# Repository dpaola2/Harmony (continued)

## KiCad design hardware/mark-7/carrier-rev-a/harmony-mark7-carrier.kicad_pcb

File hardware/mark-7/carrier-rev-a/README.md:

# Mark-7 removable Feather carrier, revision A

The first carrier design is ready for an unpowered fit review. It replaces the Feather's loose jumper connections with sockets and labeled solder pads. Dave adopted this direction on October 11, 2026. Build Mark-7 portable Bluetooth player (HARMONY-19) tracks physical acceptance.

The existing Feather, faceplate components, firmware, battery connector, and ANO cable remain in use. The carrier is a passive two-layer PCB, nominally 53.5 × 28.3 × 1.6 mm. The PCBWay Gerber package is prepared for quotation. Physical fit remains pending; no fabrication has been released. See [submission details](pcbway/README.md).

## What connects where

The Feather plugs into two female socket strips. Ten wires run between the carrier and the display/SD board. Those wires require soldering at their endpoints. The carrier removes the need to solder onto the Feather's male pins.

The ANO STEMMA QT cable connects directly to the Feather. The battery connects directly to its JST socket. P11 and R1 reserve optional ANO interrupt wiring. Leave both unused for the current cable-only sleep behavior.

| Pad | Display label / function | Feather connection |
| --- | --- | --- |
| P1 | VIN | 3V3, JP1 pin 15 |
| P2 | GND | GND, JP1 pin 13 |
| P3 | TFT CS | GPIO26, JP1 pin 12 |
| P4 | SD CS | GPIO25, JP1 pin 11 |
| P5 | LITE | GPIO4, JP1 pin 7 |
| P6 | MISO | GPIO21, JP1 pin 4 |
| P7 | MOSI | GPIO27, JP3 pin 6 |
| P8 | DC | GPIO33, JP3 pin 7 |
| P9 | RST | GPIO32, JP3 pin 9 |
| P10 | SCK | GPIO14, JP3 pin 10 |
| P11 | Optional ANO INT | GPIO34, JP1 pin 10 |

Display VIN receives Feather 3V3. The display's separate 3Vo pin stays disconnected. Display reset does not connect to Feather RESET. Firmware uses GPIO14 and GPIO27 for clock and MOSI, rather than the Feather's default SPI pins.

R1 accepts an optional 10k axial resistor between 3V3 and ANO INT. Installing it does not enable interrupt wake in firmware. The optional wake setting and physical INT lead are separate requirements.

## Mechanical changes

The modeled assembly retains the accepted 64 × 105 × 34 mm body. A revised rear tray lowers the carrier supports and raises the USB opening by 6.45 mm. The existing printed rear tray cannot directly accept this stack.

Four M2 × 6 mm self-tapping screws secure the carrier. Each screw uses a 2 mm printed spacer under its head. Nominal thread engagement is 2.4 mm. The Feather stays removable and is held by the socket contacts; retention still needs physical testing.

The selected sockets are Samtec SSW-116-01-G-S and SSW-112-01-G-S. Their body height is 8.51 mm. The model assumes a 2.54 mm plastic body on the existing male headers. These are specific socket dimensions, not a promise that any female header will fit.

Socket tails leave only 0.66 mm nominal clearance above the tray floor before solder fillets. Check actual solder height before final assembly. Wire bends, QT/JST plugs, and removal access also need a physical check.

The carrier has a cutout beneath the vendor antenna rectangle. It does not provide a full RF clearance zone. Closed-case Bluetooth range remains unqualified.

## Print and test the small fit kit first

Open [mark7-carrier-fit-kit.3mf](print/mark7-carrier-fit-kit.3mf) as geometry in the slicer. It contains eight separate objects on a 118.5 × 50.41 mm area. The file is unsliced and contains no printer settings. Use the established PLA profile; consider a brim for the narrow socket stand-ins.

| Part | Quantity | Purpose |
| --- | --- | --- |
| Mount test base | 1 | Tests the four short supports and screw engagement |
| Carrier dummy | 1 | Matches the PCB outline, thickness, and holes |
| Long socket stand-in | 1 | Represents the 16-position socket, 8.51 mm high |
| Short socket stand-in | 1 | Represents the 12-position socket, 8.51 mm high |
| Screw spacer | 4 | Adds 2 mm under each M2 × 6 screw head |

1. Use the spare Feather first. Disconnect USB and the battery.
2. Place the carrier dummy over the four supports on the test base.
3. Put one printed spacer under each M2 × 6 screw head.
4. Start all four screws, then tighten gently. Stop if a support splits or the screw bottoms out.
5. Place the long socket stand-in over the 16-hole row and the short one over the 12-hole row.
6. Align the Feather's headers with the stand-ins. Its USB socket faces the short, unnotched end of the carrier.
7. Lower the Feather gently. Do not force pins through undersized printed holes.
8. Check that the existing black header bodies rest on the socket stand-ins without bending the Feather.
9. Check that the carrier stays flat and the screws hold without protruding through the base.
10. Report any rocking, pin mismatch, blocked USB access, or interference with the screw heads.

The printed stand-ins have clearance holes, not electrical contacts. They test spacing and stack height only. Real sockets require 3.68–6.35 mm pin insertion; confirm exposed pin length before purchase. The printed test cannot qualify contact force or electrical reliability.

After this test, review the revised rear tray with the actual cable routing. Keep the working faceplate wiring intact until the physical fit is accepted. Ten suitable insulated wires will still be needed; wire stock has not been confirmed.

## Evidence and limits

- KiCad 8.0.9: zero ERC violations, zero DRC violations, and zero unconnected nets.
- Independent check: all 28 socket positions match the vendor header layout.
- Independent check: all connected PCB pads match the exported schematic netlist.
- Independent check: eight display/SD GPIO routes match the current firmware.
- Mechanical checks: 168 modeled comparisons report no collisions above the configured tolerance.
- Print checks: eight watertight single-body objects, no overlap, and a successful 3MF round trip.

These checks do not prove solderability, signal integrity, power margin, RF range, or physical fit. Socket bodies and plugs use nominal envelopes. The previously reported cracked faceplate support is not qualified by this work.

## Files and rebuilding

- `harmony-mark7-carrier.kicad_pro`, `.kicad_sch`, `.kicad_pcb`: editable KiCad project.
- `Harmony.pretty`, `Harmony.kicad_sym`: local component libraries.
- `review/schematic.pdf`: readable electrical drawing.
- `mechanical/assembly.step`: assembly model; `mechanical/tray.stl` is a candidate rear revision.
- `bom.csv`, `connections.json`: parts and pin assignments.
- `verification.json`, `mechanical/validation.json`, `print/validation.json`: check results.

Run `rebuild.sh` from this directory to rebuild the electrical files and fit kit. It uses the repository's KiCad 8.0.9 runtime and `uv`. Mechanical generation can take several minutes. Preview PNGs use the optional rendering commands in that script.

## Sources and cross-references

- [Adafruit Feather ESP32 V2 source CAD](https://github.com/adafruit/Adafruit-ESP32-Feather-V2-PCB), retained under `hardware/mark-6/carrier-rev-a/reference/`.
- [Feather pinouts](https://learn.adafruit.com/adafruit-esp32-feather-v2/pinouts).
- [Display pinouts](https://learn.adafruit.com/2-0-inch-320-x-240-color-ips-tft-display/pinouts).
- [Samtec SSW drawing](https://suddendocs.samtec.com/catalog_english/ssw_th.pdf): socket dimensions and insertion limits. Stock and pricing are not verified.
- [Mark-7 scope](../../../docs/mark-7-portable-scope.md).
- [Power and sleep](../../../docs/mark-7-power-and-sleep.md).
- [Previous rear design](../../../enclosure/mark-7/rear-review-c/README.md).

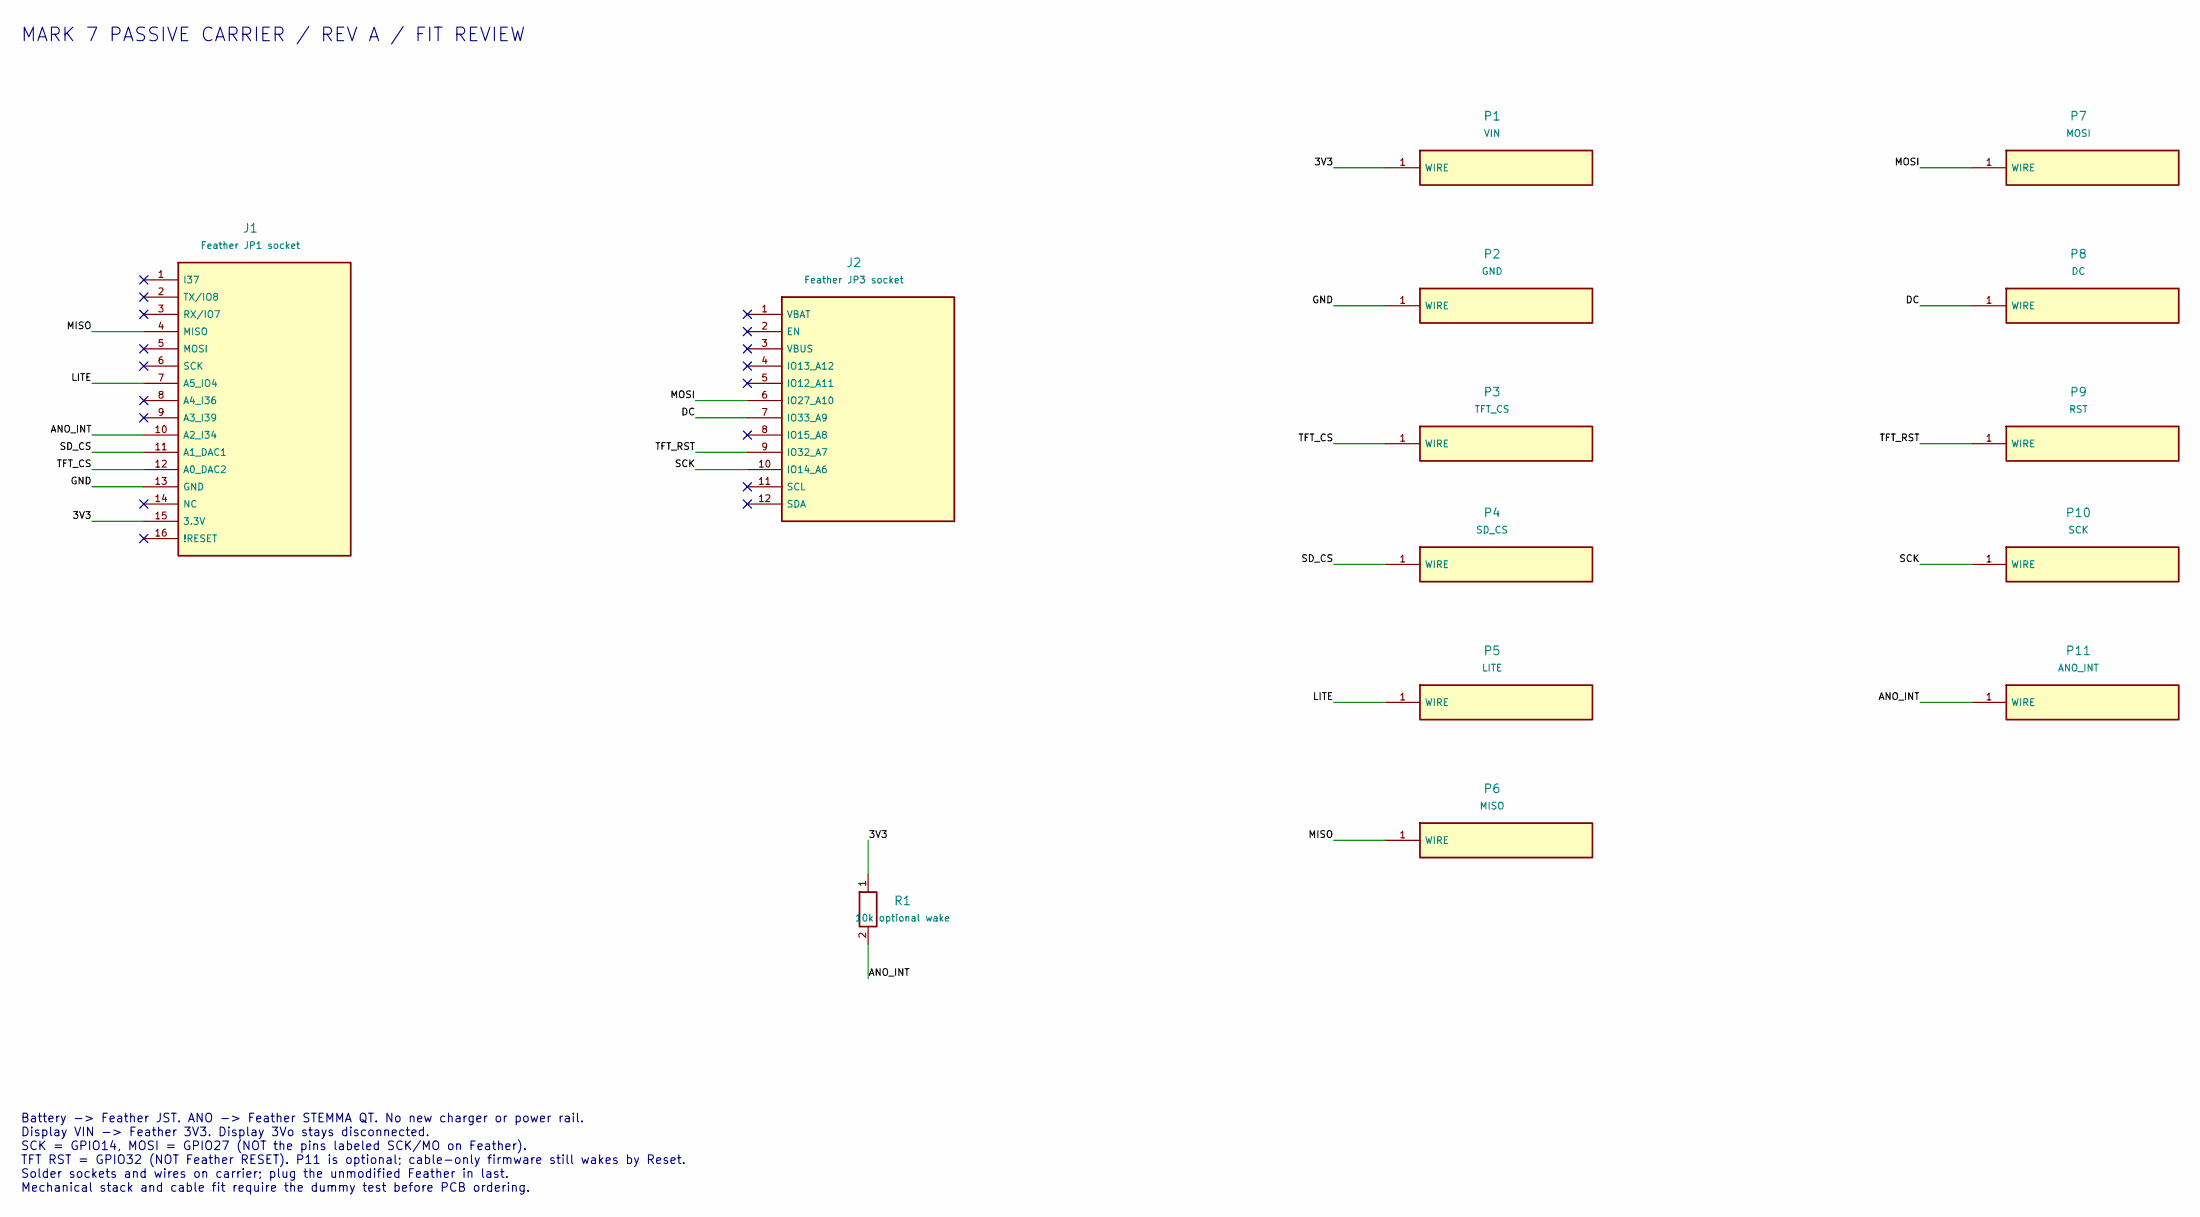
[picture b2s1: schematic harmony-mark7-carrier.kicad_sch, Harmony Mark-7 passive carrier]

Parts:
J1: Feather JP1 socket; Feather_JP1; MPN SSW-116-01-G-S
J2: Feather JP3 socket; Feather_JP3; MPN SSW-112-01-G-S
P1: VIN; WirePad
P2: GND; WirePad
P3: TFT_CS; WirePad
P4: SD_CS; WirePad
P5: LITE; WirePad
P6: MISO; WirePad
P7: MOSI; WirePad
P8: DC; WirePad
P9: RST; WirePad
P10: SCK; WirePad
P11: ANO_INT; WirePad
R1: 10k optional wake; R_Axial_P7.62

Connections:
3V3: J1.15 (3.3V), P1.1, R1.1
ANO_INT: J1.10 (A2_I34), P11.1, R1.2
DC: J2.7 (IO33_A9), P8.1
GND: J1.13 (GND), P2.1
LITE: J1.7 (A5_IO4), P5.1
MISO: J1.4 (MISO), P6.1
MOSI: J2.6 (IO27_A10), P7.1
SCK: J2.10 (IO14_A6), P10.1
SD_CS: J1.11 (A1_DAC1), P4.1
TFT_CS: J1.12 (A0_DAC2), P3.1
TFT_RST: J2.9 (IO32_A7), P9.1

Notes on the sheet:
MARK 7 PASSIVE CARRIER / REV A / FIT REVIEW
Battery -> Feather JST. ANO -> Feather STEMMA QT. No new charger or power rail. Display VIN -> Feather 3V3. Display 3Vo stays disconnected. SCK = GPIO14, MOSI = GPIO27 (NOT the pins labeled SCK/MO on Feather). TFT RST = GPIO32 (NOT Feather RESET). P11 is optional; cable-only firmware still wakes by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

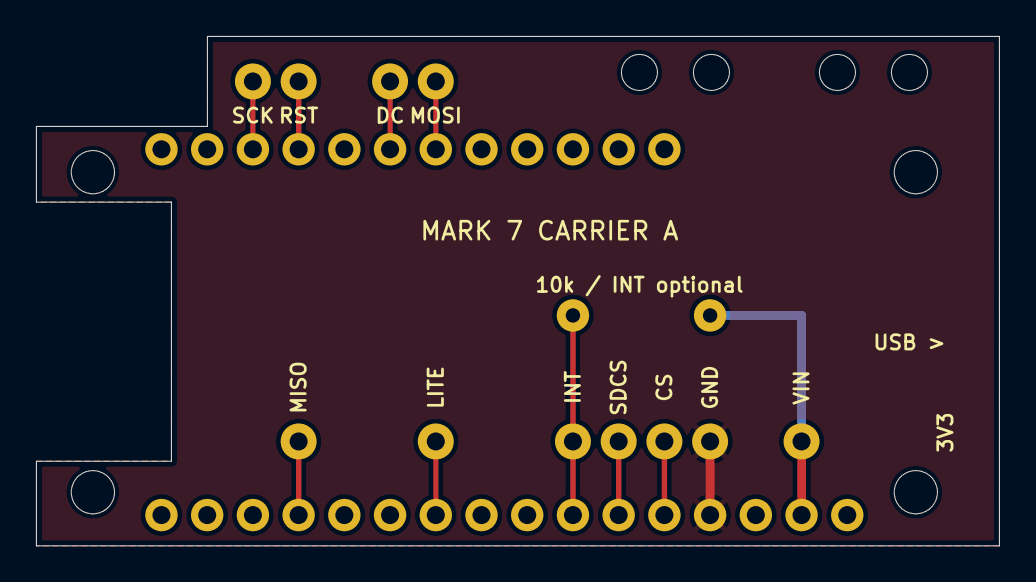
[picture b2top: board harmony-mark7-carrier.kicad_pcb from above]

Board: 2 copper layers, 53.5 x 28.3 mm, 22 parts (0 on the bottom side), 11 nets.

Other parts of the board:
H1, H2, H3, H4: M2 mount; Mount
S1, S2, S3, S4: Cable tie; Tie

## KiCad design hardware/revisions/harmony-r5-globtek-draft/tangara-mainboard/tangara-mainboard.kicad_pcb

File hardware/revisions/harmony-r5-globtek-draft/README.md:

# Harmony R5 GlobTek draft

U10 changed to MCP73871-1CCI/ML in schematic and PCB MPN property. Routed geometry and connectivity unchanged from R4. Local integration draft; not submitted or released. Temperature-sensor qualification remains open. See ../../procurement/globtek-integration/README.md.

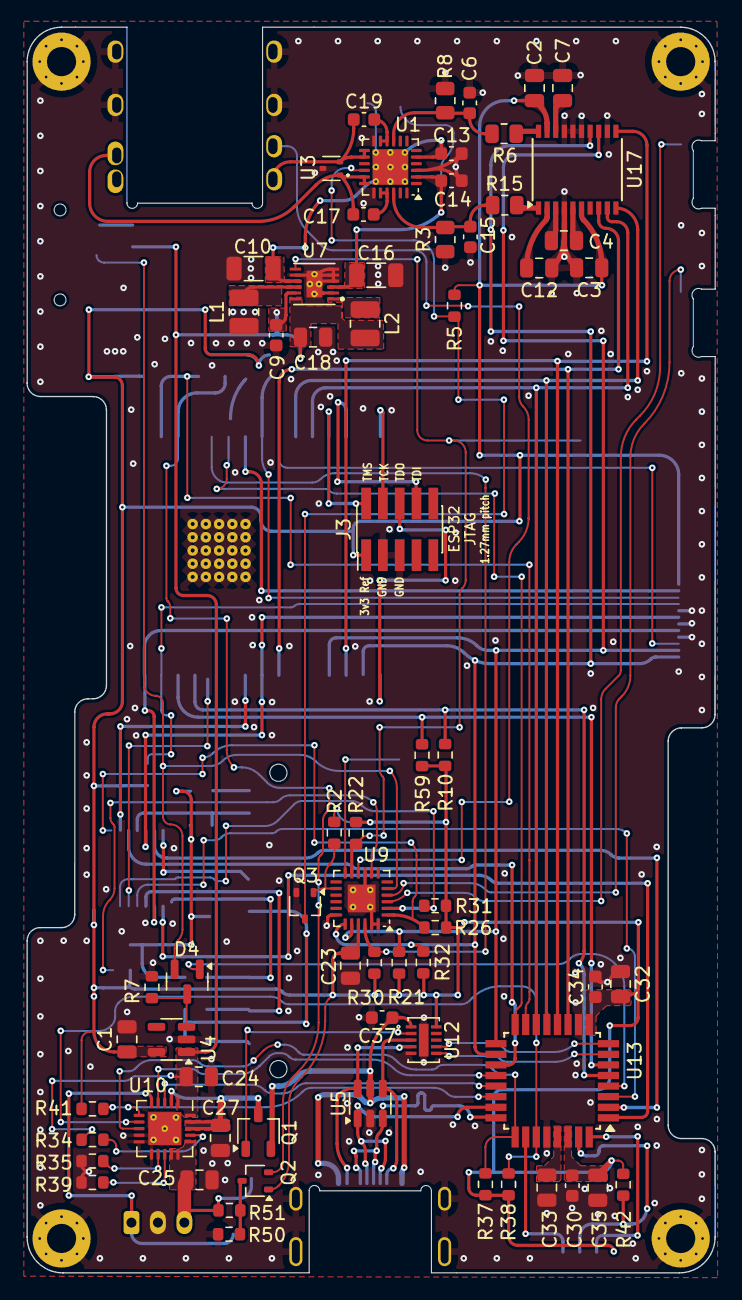
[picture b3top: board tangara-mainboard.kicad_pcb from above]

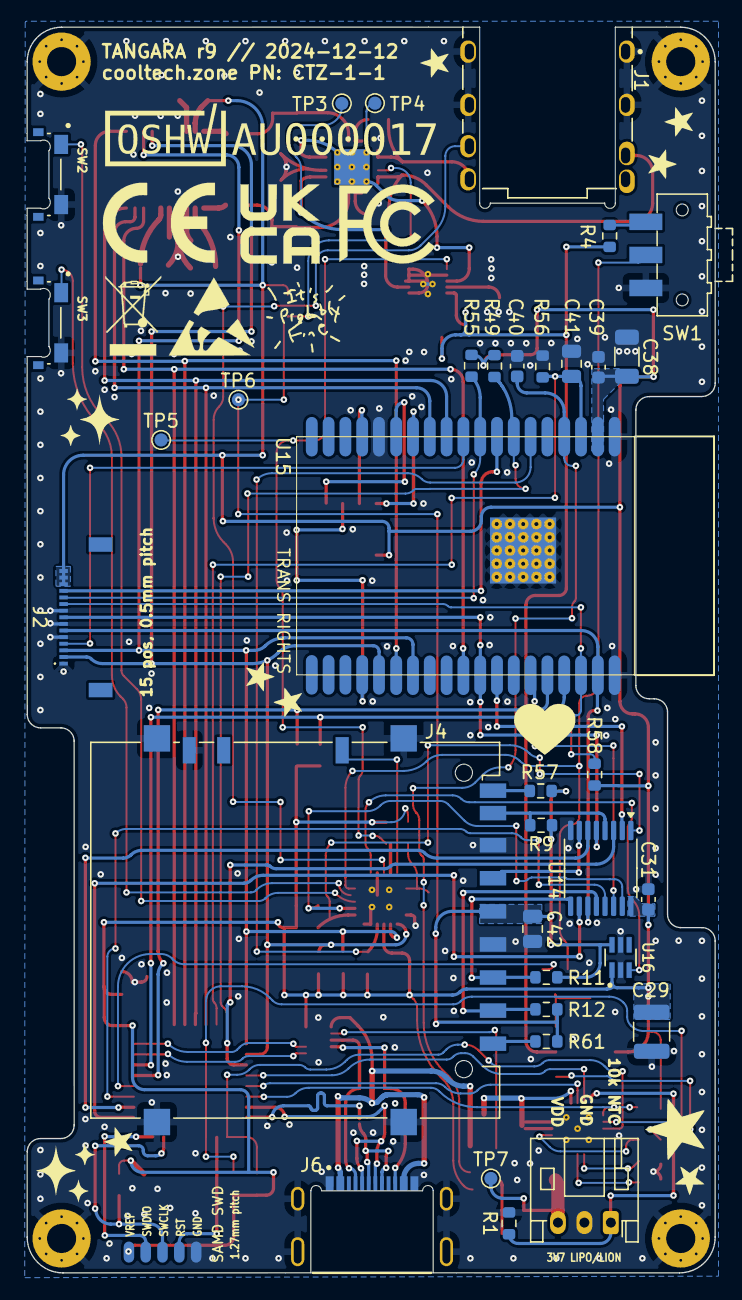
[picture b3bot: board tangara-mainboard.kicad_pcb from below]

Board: 4 copper layers, 52.0 x 94.2 mm, 106 parts (35 on the bottom side), 92 nets.

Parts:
C1, C2, C3, C7, C18, C24, C25, C27, C32, C35, C42: 10μF; C_0805_2012Metric
C4, C12, C23, C33, C41: 1μF; C_0805_2012Metric
C6, C15: 2700pF; C_0603_1608Metric
C9, C13, C14, C30, C31, C34, C37, C39, C40: 0.1μF; C_0603_1608Metric
C10, C16, C38: 22μF; C_1206_3216Metric
C17, C19: 100pF; C_0603_1608Metric
C29: 100uF; C_1210_3225Metric
D4: BAT54C; SOT-23
H1, H2, H3, H4: MountingHole; MountingHole_2.2mm_M2_Pad_Via2
J1: SJ-3506-SMT; CUI_SJ-3506-SMT
J2: FP Connector; G-Switch GT-F0509SR15-15SMT01
J3: JTAG; PinHeader_2x05_P1.27mm_Vertical_SMD
J4: SD_Card; SD_Hirose_DM1AA_SF_PEJ82
J5: SWD; SAMDSWD
J6: USB; GCT_USB4510-03-1-A_REVA
J7: Battery; JST_PH_S3B-PH-K_1x03_P2.00mm_Horizontal
L1, L2: 4.7μH; L_1008_2520Metric
Q1: PMV48XPA2R; TSOT-23
Q2, Q3: PJC138K; SOT-323_SC-70
R1, R2, R4, R5, R9, R10, R11, R12, R21, R22, R26, R30, R31, R32, R34, R35, R37, R38, R41, R49, R55, R57, R58, R59, R61: 10kΩ; R_0603_1608Metric
R3, R8: 2.2kΩ; R_0805_2012Metric
R6, R15: 560Ω; R_0805_2012Metric
R7, R50, R51, R56: 1MΩ; R_0603_1608Metric
R39, R42: 1kΩ; R_0603_1608Metric
SW1: SW_SPDT; SW_SPDT_CK-JS102011SAQN
SW2, SW3: SW_Push; SW_EVQ-P4HB3B
TP3: +5V; TestPoint_Pad_D1.0mm
TP4: -5V; TestPoint_Pad_D1.0mm
TP5: AMP_EN; TestPoint_Pad_D1.0mm
TP6: AMP_MUTE; TestPoint_Pad_D1.0mm
TP7: BAT; TestPoint_Pad_D1.0mm
U1: INA1620; QFN-24-1EP_4x4mm_P0.5mm_EP2.7x2.7mm_ThermalVias
U3: D5V0L2B3T-7; SOT-523
U4: TLV75533PDBV; SOT-23-5
U5: PE1605C4A6; SOT-23-6
U7: TPS65133; SON40P300X300X80-13N
U9: PCA8575; HVQFN-24-1EP_4x4mm_P0.5mm_EP2.1x2.1mm
U10: MCP73871; QFN-20-1EP_4x4mm_P0.5mm_EP2.5x2.5mm_ThermalVias2
U12: BD91N01NUX; BD91N01NUX-E2
U13: ATSAMD21E18A-AF; TQFP-32_7x7mm_P0.8mm
U14: 74CBTLV3257; TSSOP-16_4.4x5mm_P0.65mm
U15: ESP32-WROVER-E; ESP32-WROVER
U16: TPS22948; SOT65P210X110-6N
U17: WM8523; SSOP-20_4.4x6.5mm_P0.65mm

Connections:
3.5mm_DETECT: J1.4, U9.10 (IO1_0)
+3V3: C1.1, C2.2, C3.1, C23.1, C29.1, C30.1, C31.1, C32.2, C34.1, C35.2, C38.1, C39.1, J2.13, J2.14, J2.15, J3.1 (vRef), J5.1, Q2.1 (G), R2.2, R5.1, R10.1, R21.1, R22.2, R26.1, R30.1, R31.1, R32.1, R37.1, R38.1, R41.1, R42.1, R49.1, R55.1, R58.1, R59.1, U4.5 (OUT), U9.21 (VDD), U12.10 (VDD_IO), U13.9 (VDDANA), U13.30 (VDDIN), U14.16 (VCC), U15.2 (VDD), U16.1 (IN), U17.6 (LINEVDD), U17.19 (AVDD)
+5VA: C14.1, C16.1, TP3.1, U1.2 (V+), U7.3 (VPOS)
-5VA: C10.2, C13.1, TP4.1, U1.5 (V-), U1.25 (EP), U7.9 (VNEG)
/ESP_EN: C41.1, R56.2, U13.15 (PA14), U15.3 (EN)
/JTAG.TCK: J3.4 (TCK), U15.16 (JTAG.TCK)
/JTAG.TDI: J3.8 (TDI), U15.14 (JTAG.TDI)
/JTAG.TDO: J3.6 (TDO), U15.23 (JTAG.TDO)
/JTAG.TMS: J3.2 (TMS), U15.13 (JTAG.TMS)
/Power/NTC: J7.1, R1.1, U10.5 (THERM)
/Power/VBUS_SWITCHED: C27.1, Q1.3 (D), U10.2 (VPCC), U10.18 (IN), U10.19 (IN)
/SWD.RESET: J5.4, U13.26 (~RESET)
/SWD.SWCLK: J5.3, R42.2, U13.31 (SWCLK)
/SWD.SWDIO: J5.2, U13.32 (SWDIO)
/UART.ESP.RX: R10.2, U13.5 (PA04(SERCOM0.0)), U15.34 (UART.RX)
/UART.ESP.TX: R59.2, U13.6 (PA05(SERCOM0.1)), U15.35 (UART.TX)
/~SAMD_INT: R49.2, U13.16 (PA15), U15.7 (I35)
AMP_EN: R22.1, TP5.1, U7.7 (EN), U9.11 (IO1_1)
AMP_MUTE: Q3.3 (D), R5.2, TP6.1, U1.16 (EN)
BAT_LEVEL: C40.2, Q2.2 (S), U15.4 (ADC1_CH0/NOINT)
CHG_PROG: U10.4 (PROG2), U13.20 (PA19)
CHG_SEL: U10.3 (SEL), U13.21 (PA22)
CHG_STAT1: R37.2, U10.8 (STAT1/~LBO), U13.25 (PA27)
CHG_STAT2: R38.2, U10.7 (STAT2), U13.27 (PA28)
DAC.BCK: U13.13 (PA10(I2S/SCK)), U15.11 (I2S.BCK), U17.10 (BCLK)
DAC.DATA: U13.11 (PA08(I2S/SD)), U15.29 (I2S.DOUT), U17.8 (DACDAT)
DAC.LRCK: U13.14 (PA11(IS2/FS)), U15.12 (I2S.LRCK), U17.9 (LRCLK)
DAC.MCK: U13.12 (PA09(I2S/MCK)), U15.25 (BOOT/I2S.SCK), U17.11 (MCLK)
DISPLAY_DR: J2.11, R55.2, U15.9 (IO33)
DISPLAY_LED_EN: J2.12, U15.8 (IO32)
ESP_SPI.DISPLAY_CS: J2.10, R58.2, U15.36 (SPI.CS1)
ESP_SPI.PICO: J2.6, U14.11, U15.37 (SPI.PICO)
ESP_SPI.POCI: U14.2, U15.31 (SPI.POCI)
ESP_SPI.SCLK: J2.8, U14.5, U15.30 (SPI.CLK)
ESP_SPI.SD_CS: U14.14, U15.33 (SPI.CS0)
GND: C1.2, C2.1, C3.2, C6.1, C7.2, C9.2, C10.1, C12.1, C13.2, C14.2, C15.1, C16.2, C18.2, C23.2, C24.2, C25.2, C27.2, C29.2, C30.2, C31.2, C32.1, C33.1, C34.2, C35.1, C37.2, C38.2, C39.2, C40.1, C41.2, C42.2, H1.1, H2.1, H3.1, H4.1, J1.1, J1.5, J1.SH1, J1.SH2, J2.1, J2.5, J2.7, J2.9, J3.3 (GND), J3.5 (GND), J4.3 (VSS), J4.6 (VSS), J4.SH, J4.SW, J5.5, J6.A1_B12 (GND), J6.B1_A12 (GND), J6.S1 (SHELL_GND), J6.S2 (SHELL_GND), J6.S3 (SHELL_GND), J6.S4 (SHELL_GND), J7.2, L1.1, Q3.2 (S), R1.2, R3.1, R7.1, R8.1, R35.2, R39.2, R50.2, R56.1, SW1.1 (A), SW2.2, SW3.2, U1.3 (GND), U1.12, U1.19, U3.3, U4.2 (GND), U5.2 (GND), U7.2 (PGND), U7.4 (GND), U7.5 (AGND), U7.6 (GND), U7.8 (GND), U7.13 (EXP), U9.9 (VSS), U9.18 (A0), U9.23 (A1), U9.24 (A2), U9.25 (EP), U10.9 (~TE), U10.10 (V_{SS}), U10.11 (V_{SS}), U10.21 (V_{SS}), U12.5 (GND), U12.11 (EP), U13.10 (GND), U13.28 (GND), U14.8 (GND), U15.1 (GND), U15.15 (GND), U15.38 (GND), U15.39 (GND), U16.2 (GND), U16.5 (FLT), U17.4 (LINEGND), U17.12 (SDOUT/DEEMPH), U17.15 ({~CS}/{~MUTE}), U17.16 (CIFMODE), U17.17 (AGND)
I2C.SCL: J2.2, R26.2, U9.19 (SCL), U13.18 (PA17(SERCOM3.1)), U15.24 (I2C.SCL), U17.14 (SCLK)
I2C.SDA: J2.3, R21.2, U9.20 (SDA), U13.17 (PA16(SERCOM3.0)), U15.26 (I2C.SDA), U17.13 (SDA)
KEY_LOCK: D4.2, SW1.2 (B), U9.5 (IO0_4)
KEY_VOL_DOWN: SW3.1, U9.4 (IO0_3)
KEY_VOL_UP: SW2.1, U9.3 (IO0_2)
unnamed: C17.2, J1.2, U1.17, U1.18, U3.1
unnamed: C19.2, J1.3, U1.13, U1.14, U3.2
unnamed: J4.1 (CD/DAT3), R12.2, U14.12
unnamed: J4.5 (CLK), U14.7
unnamed: J4.2 (CMD), R11.2, U14.9
unnamed: J4.7 (DAT0), R9.2, U14.4
unnamed: J4.8 (DAT1), R57.2
unnamed: J4.9 (DAT2), R61.2
unnamed: C42.1, J4.4 (VDD), R9.1, R11.1, R12.1, R57.1, R61.1, U16.6 (OUT)
unnamed: J6.A5 (CC1), U5.4 (IO3), U12.3 (CC1)
unnamed: J6.B5 (CC2), U5.6 (IO5), U12.4 (CC2)
unnamed: C25.1, J7.3, R51.1, TP7.1, U10.14 (V_{BAT}), U10.15 (V_{BAT}), U10.16 (V_{BAT_SENSE})
unnamed: Q1.1 (G), U12.2 (SWDRV)
unnamed: Q2.3 (D), R50.1, R51.2
unnamed: Q3.1 (G), R2.1, U9.14 (IO1_4)
unnamed: R4.1, SW1.3 (C)
unnamed: C15.2, R3.2, R15.2, U1.22 (+)
unnamed: C17.1, U1.20, U1.21 (-)
unnamed: C6.2, R6.2, R8.2, U1.9 (+)
unnamed: C19.1, U1.10 (-), U1.11
unnamed: D4.3, R7.2, U4.3 (EN)
unnamed: L1.2, U7.10 (SWN)
unnamed: L2.1, U7.1 (SWP)
unnamed: R34.2, U10.17 (CE)
unnamed: R39.1, U10.13 (PROG1)
unnamed: R35.1, U10.12 (PROG3)
unnamed: C33.2, U13.29 (VDDCORE)
unnamed: R32.2, U9.1 (IO0_0), U14.1 (S)
unnamed: R31.2, U9.2 (IO0_1), U14.15 (~OE)
unnamed: C4.1, U17.5 (CPCA)
unnamed: C4.2, U17.3 (CPCB)
unnamed: C12.2, U17.2 (CPVOUTN)
unnamed: R15.1, U17.1 (LINEVOUTL)
unnamed: R6.1, U17.20 (LINEVOUTR)
unnamed: C7.1, U17.18 (VMID)
SAMD_SPI.CS: U13.3 (PA02), U14.13
SAMD_SPI.PICO: U13.1 (PA00(SERCOM1.0)), U14.10
SAMD_SPI.POCI: U13.19 (PA18(SERCOM1.2)), U14.3
SAMD_SPI.SCLK: U13.2 (PA01(SERCOM1.1)), U14.6
SD_CD: J4.CP, U9.12 (IO1_2)
SYS_POWER: C9.1, C18.1, C24.1, L2.2, R4.2, R34.1, U4.1 (IN), U7.11 (AVIN), U7.12 (PVIN), U10.1 (OUT), U10.20 (OUT)
SYS_PWR_EN_SAMD: D4.1, U13.4 (PA03)
USB.DN: J6.A7 (DN), J6.B7 (DN), U5.1 (IO1), U13.23 (USB.DM)
USB.DP: J6.A6 (DP), J6.B6 (DP), U5.3 (IO2), U13.24 (USB.DP)
USB_TCC0: U12.7 (TCC0), U13.8 (PA07)
USB_TCC1: U12.6 (TCC1), U13.7 (PA06)
VBUS: C37.1, J6.A4_B9 (VBUS), J6.B4_A9 (VBUS), Q1.2 (S), U5.5 (IO4), U12.1 (VBUS)
~CHG_PWR_OK: R41.2, U10.6 (~PG), U13.22 (PA23)
~GPIO_INT: R30.2, U9.22 (~INT), U15.6 (I34)
~SD_VDD_EN: U9.8 (IO0_7), U16.3 (ON)
~TOUCH_INT: J2.4, U15.10 (IO25)

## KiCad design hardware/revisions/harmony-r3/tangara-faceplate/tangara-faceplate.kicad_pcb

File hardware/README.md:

# Hardware Notes

## Prototypes
- Prototype 1: ESP32-S3-WROOM DevKitC-1 v1.1, SD SPI, ST7789V2 (1.69", 240x280), basic buttons, USB power. No audio/A2DP (S3 WROOM lacks classic BT); focus on UI/SD/display.
- Prototype 2: ESP32-WROVER DevKitC (PSRAM, classic BT) for audio/A2DP; SD SPI, ST7789 (2.0–2.4"), rotary encoder + buttons, optional I2S DAC/amp; USB or LiPo/TP4056 later.

## Volume Input Options
- Buttons: dedicated volume up/down buttons produce relative events; core clamps 0–100 and calls `set_volume`.
- Encoder-as-volume: use a second rotary (or mode switch) to emit relative steps; map to the same core events.
- Absolute knob (potentiometer): yields an analog value; platform adapter should translate ADC reading to a clamped 0–100 and push into core via `set_volume` (core supports absolute level set).

## Power System
- Battery: LiPo 1000–2000 mAh flat cell.
- Charging: TP4056 (USB-C variant) for LiPo charging.
- Regulation: ESP32 dev board regulator or MT3608 step-up if 5V needed for peripherals.
- Power switch: SPDT slide/lockable on/off.
- Optional: battery voltage sensing via ADC for future battery UI; plan GPIO and resistor divider.

## Notes/Next Steps
- Wiring: document GPIO mapping for encoder, buttons, SD (SPI), display (SPI), and optional I2S pins.
- Bluetooth A2DP: confirm ESP32 MicroPython support vs ESP-IDF shim; may need C-extension for stable source mode.
- Settings persistence: volume, last track, etc., stored in flash/SD (JSON) on device; core ready once adapters persist/load.

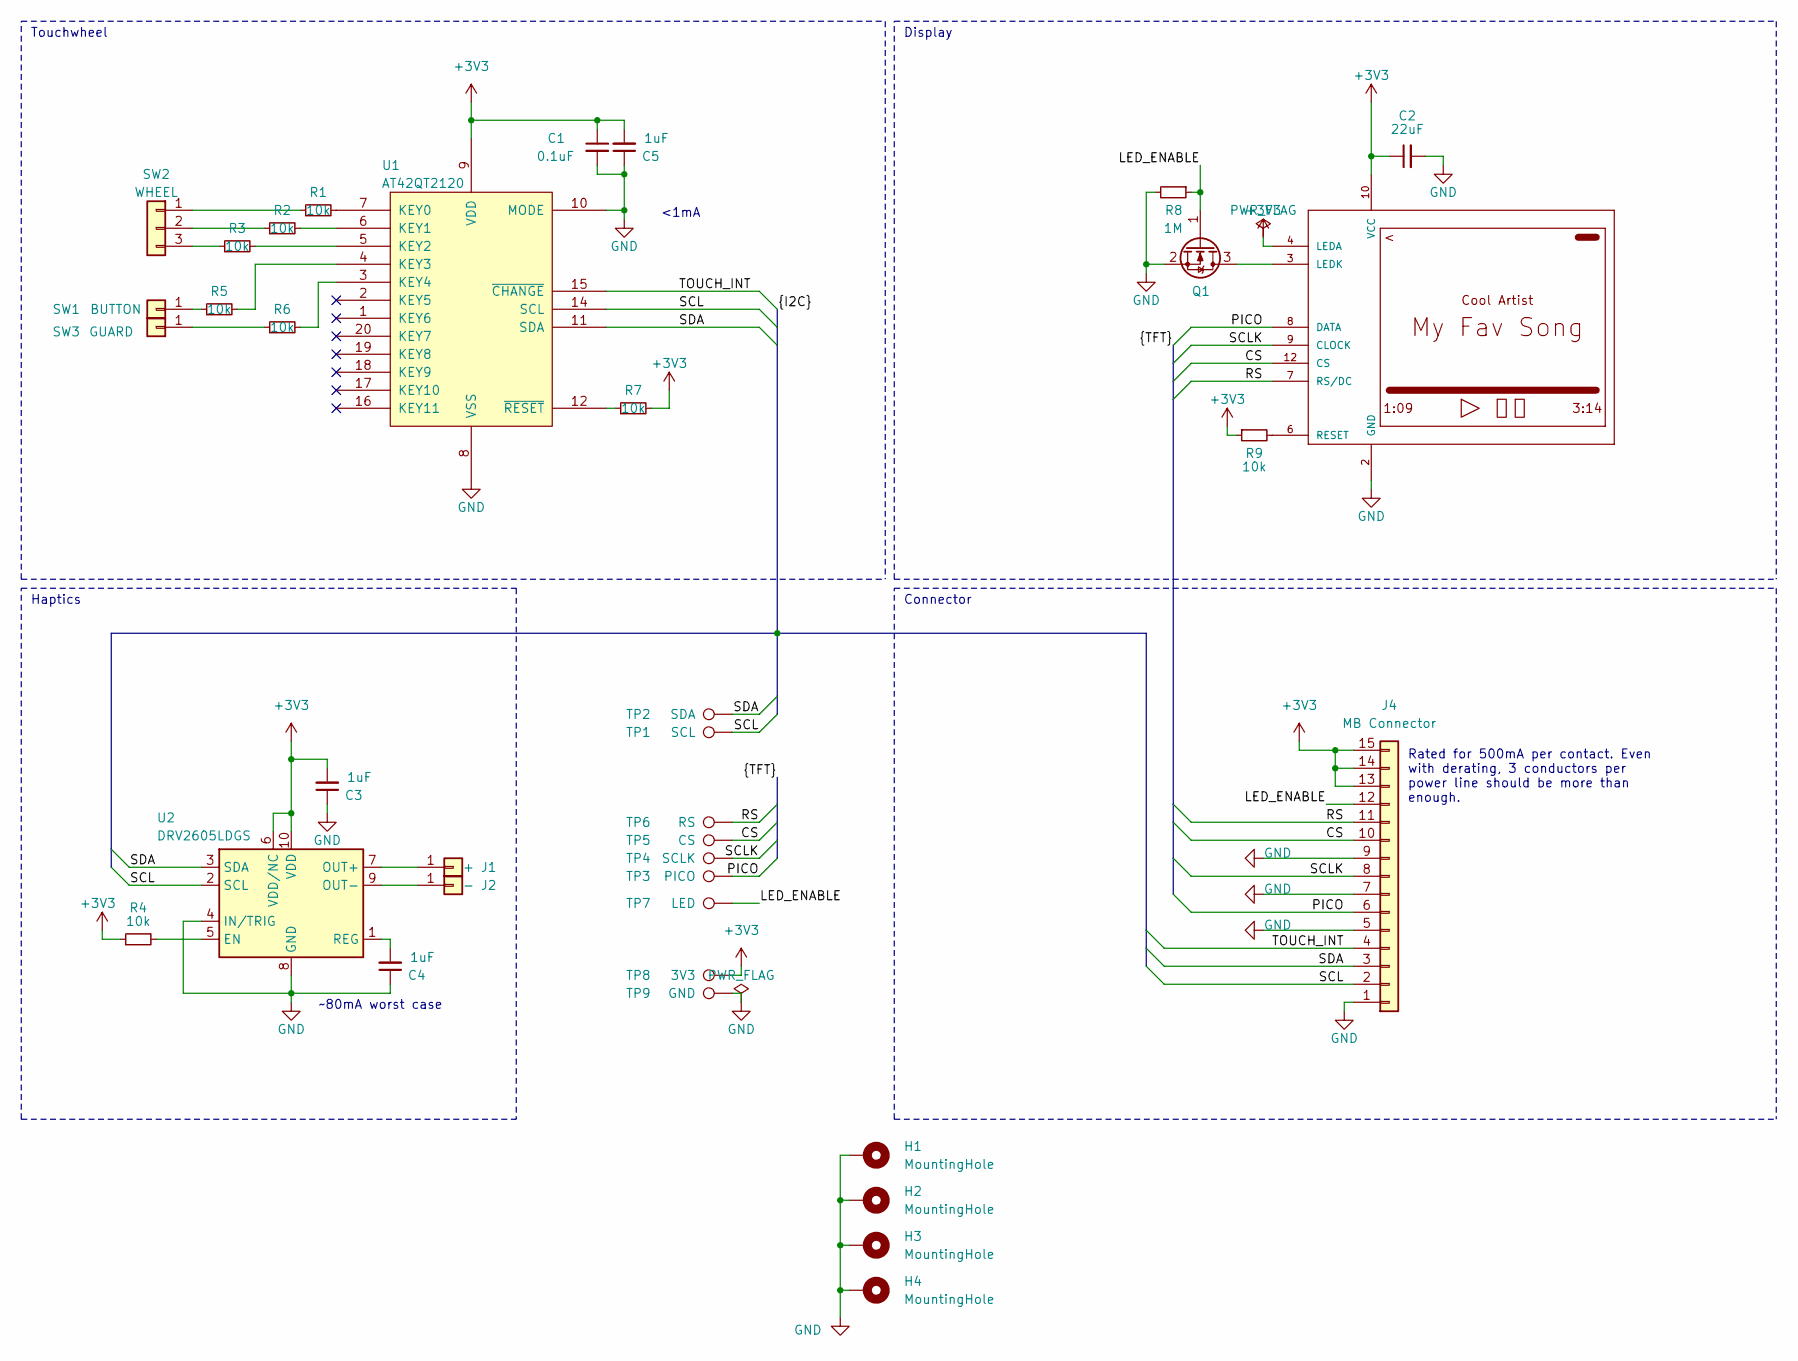
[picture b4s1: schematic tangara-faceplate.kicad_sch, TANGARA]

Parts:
C1: 0.1uF; C_0603_1608Metric; MPN GCM188R71C104KA37J
C2: 22uF; C_1206_3216Metric; MPN GRM319R61C226KE15D
C3, C4, C5: 1uF; C_0805_2012Metric; MPN GRM216R61C105KA88D
H1, H2, H3, H4: MountingHole; MountingHole_2.2mm_M2_Pad_Via
J1: +; TestPoint_Pad_D1.5mm
J2: -; TestPoint_Pad_D1.5mm
J4: MB Connector; G-Switch GT-F0509SR15-15SMT01; MPN GT-F0509SR15-15SMT01
LCD1: JD-T1800
Q1: PJC138K; SOT-323_SC-70; MPN PJC138K_R1_00001
R1, R2, R3, R4, R5, R6, R7, R9: 10k; R_0603_1608Metric; MPN AC0603JR-0710KL
R8: 1M; R_0603_1608Metric; MPN AC0603FR-131ML
SW1: BUTTON; qtouch-button
SW2: WHEEL; qtouch-wheel
SW3: GUARD; qtouch-guard
TP1: SCL; TestPoint_Pad_D1.0mm
TP2: SDA; TestPoint_Pad_D1.0mm
TP3: PICO; TestPoint_Pad_D1.0mm
TP4: SCLK; TestPoint_Pad_D1.0mm
TP5: CS; TestPoint_Pad_D1.0mm
TP6: RS; TestPoint_Pad_D1.0mm
TP7: LED; TestPoint_Pad_D1.0mm
TP8: 3V3; TestPoint_Pad_D1.0mm
TP9: GND; TestPoint_Pad_D1.0mm
U1: AT42QT2120; VQFN-20-1EP_3x3mm_P0.45mm_EP1.55x1.55mm; MPN AT42QT2120-MMH
U2: DRV2605LDGS; VSSOP-10_3x3mm_P0.5mm; MPN DRV2605LDGST

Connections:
+3V3: C1.1, C2.1, C3.2, C5.2, J4.13, J4.14, J4.15, LCD1.4 (LEDA), LCD1.10 (VCC), LCD1.11 (VCC2), R4.1, R7.2, R9.1, TP8.1, U1.9 (VDD), U2.6 (VDD/NC), U2.10 (VDD)
/CS: J4.10, LCD1.12 (CS), TP5.1
/LED_ENABLE: J4.12, Q1.1 (G), R8.1, TP7.1
/PICO: J4.6, LCD1.8 (DATA), TP3.1
/RS: J4.11, LCD1.7 (RS/DC), TP6.1
/SCL: J4.2, TP1.1, U1.14 (SCL), U2.2 (SCL)
/SCLK: J4.8, LCD1.9 (CLOCK), TP4.1
/SDA: J4.3, TP2.1, U1.11 (SDA), U2.3 (SDA)
/TOUCH_INT: J4.4, U1.15 (~CHANGE)
GND: C1.2, C2.2, C3.1, C4.1, C5.1, H1.1, H2.1, H3.1, H4.1, J4.1, J4.5, J4.7, J4.9, LCD1.2 (GND), LCD1.5 (GND1), LCD1.13 (GND2), Q1.2 (S), R8.2, TP9.1, U1.8 (VSS), U1.10 (MODE), U2.4 (IN/TRIG), U2.8 (GND)
unnamed: J1.1, U2.7 (OUT+)
unnamed: J2.1, U2.9 (OUT-)
unnamed: LCD1.3 (LEDK), Q1.3 (D)
unnamed: LCD1.6 (RESET), R9.2
unnamed: R5.1, SW1.1
unnamed: R1.1, SW2.1
unnamed: R2.1, SW2.2
unnamed: R3.1, SW2.3
unnamed: R6.1, SW3.1
unnamed: R1.2, U1.7 (KEY0)
unnamed: R2.2, U1.6 (KEY1)
unnamed: R3.2, U1.5 (KEY2)
unnamed: R5.2, U1.4 (KEY3)
unnamed: R6.2, U1.3 (KEY4)
unnamed: R7.1, U1.12 (~RESET)
unnamed: R4.2, U2.5 (EN)
unnamed: C4.2, U2.1 (REG)

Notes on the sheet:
Haptics
Touchwheel
~80mA worst case
Connector
Display
Rated for 500mA per contact. Even with derating, 3 conductors per power line should be more than enough.
<1mA

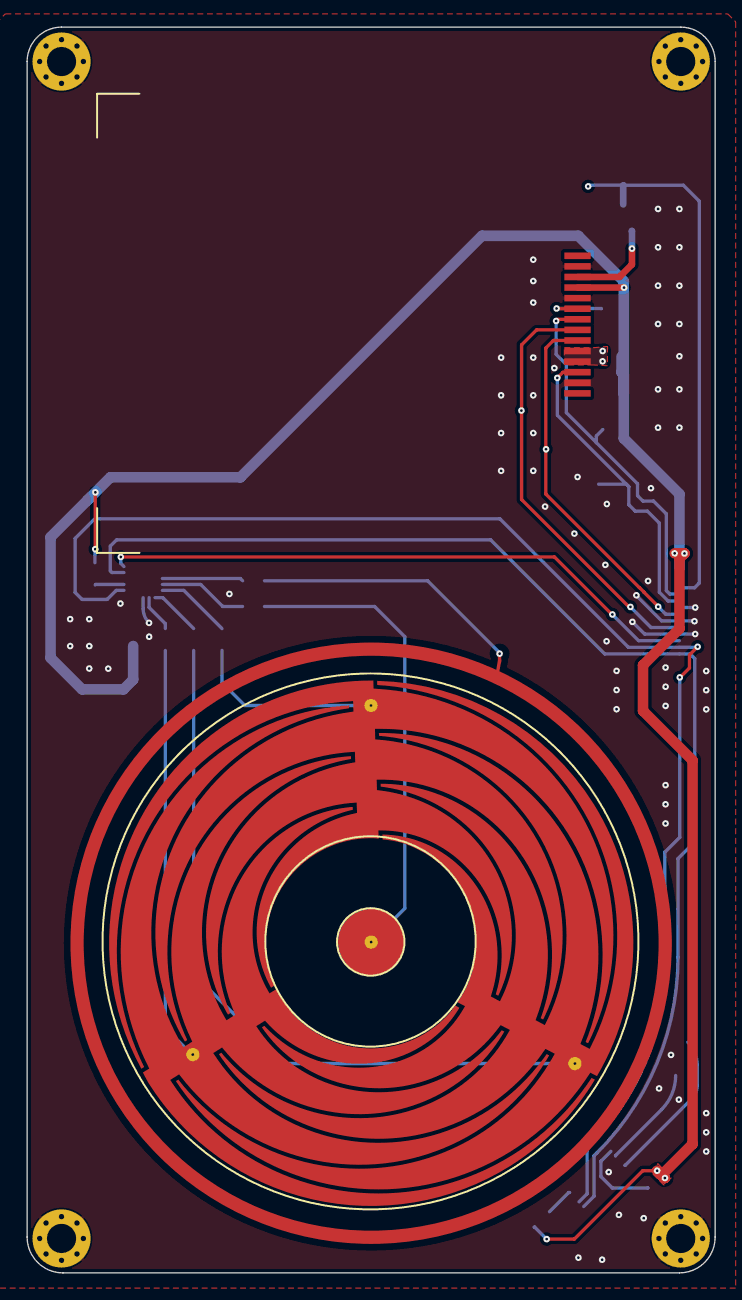
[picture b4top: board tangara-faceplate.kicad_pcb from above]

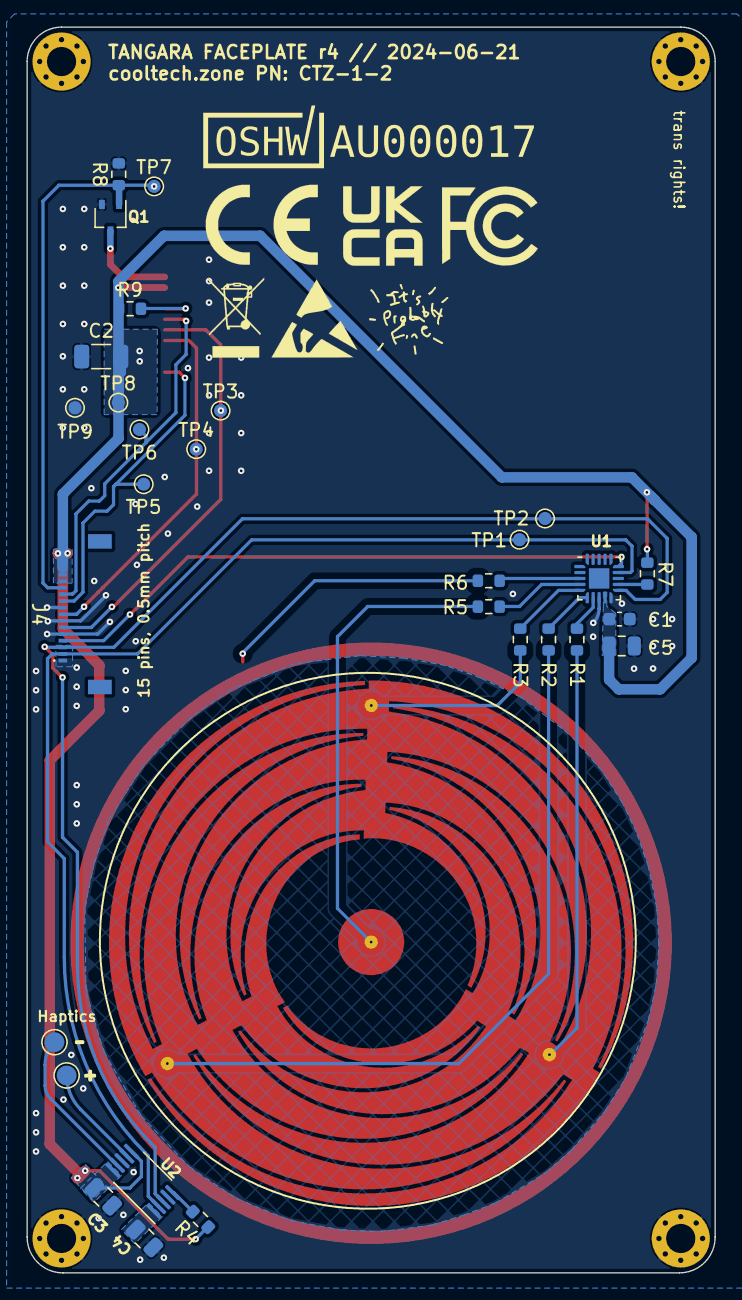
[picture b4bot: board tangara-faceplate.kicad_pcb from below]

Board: 2 copper layers, 52.0 x 94.2 mm, 39 parts (31 on the bottom side), 27 nets.

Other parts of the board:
kibuzzard-63E31E51: G***; kibuzzard-63E31E51
kibuzzard-63E31E57: G***; kibuzzard-63E31E57
